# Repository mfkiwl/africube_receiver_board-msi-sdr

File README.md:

This Repository has the Africube SDR Recever Boards V1.0 and v2 <br>
Project is compleet but boards has not been build yet 3 Feb 2021
<br>

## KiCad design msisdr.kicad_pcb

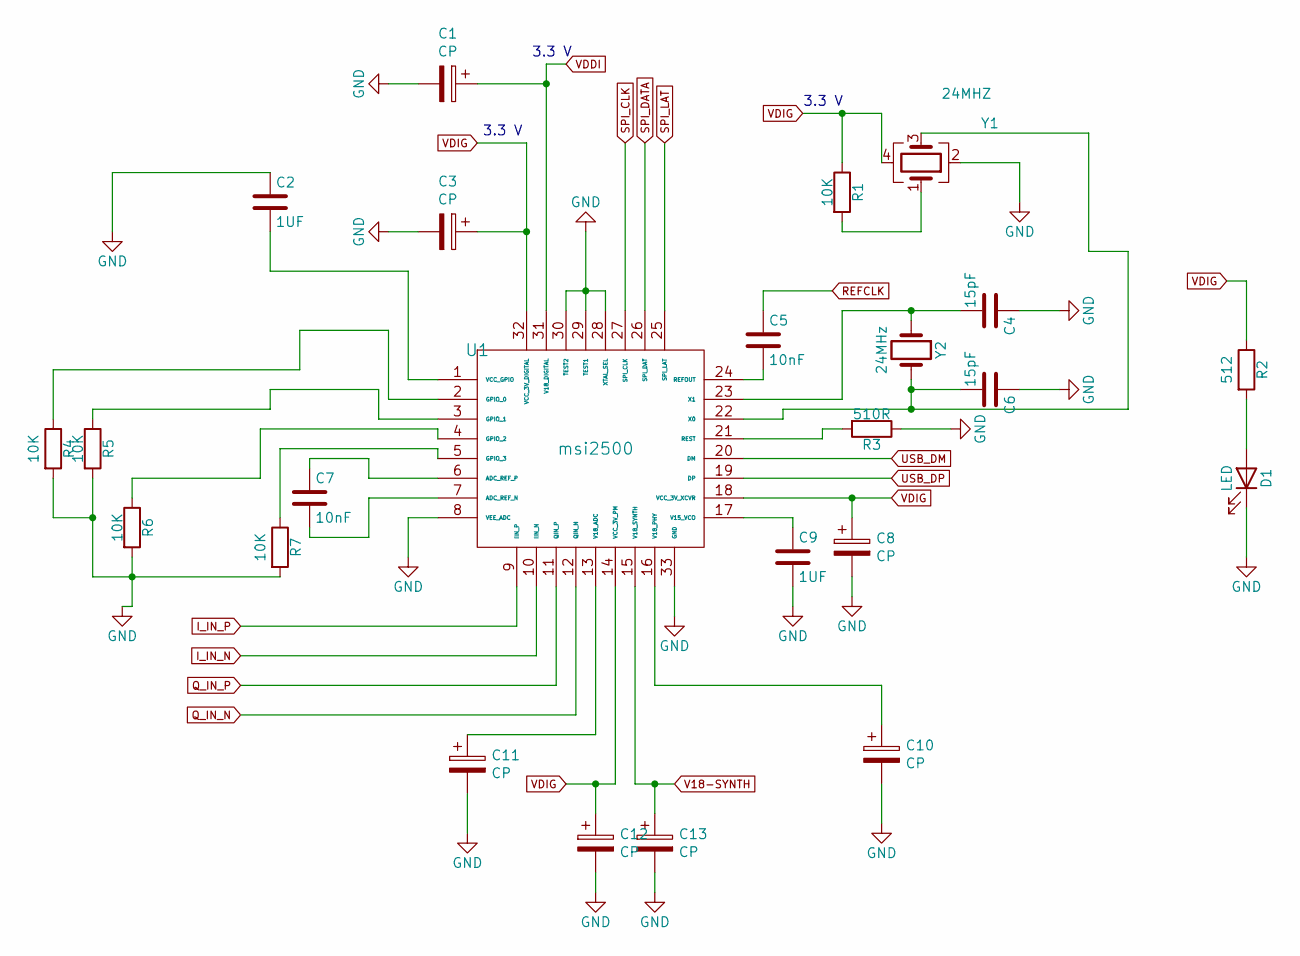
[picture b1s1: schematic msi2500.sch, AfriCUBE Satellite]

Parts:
C1, C3, C8, C10, C11, C12, C13: CP; CP_EIA-2012-12_Kemet-R
C2, C9: 1UF; C_0805_2012Metric
C4, C6: 15pF; C_0805_2012Metric
C5, C7: 10nF; C_0805_2012Metric
D1: LED; LED_0805_2012Metric
R1, R4, R5, R6, R7: 10K; R_0805_2012Metric
R2: 512; R_0805_2012Metric
R3: 510R; R_0805_2012Metric
U1: msi2500; QFN-32-1EP_5x5mm_P0.5mm_EP3.1x3.1mm
Y1: 24MHZ; Crystal_SMD_7050-4Pin_7.0x5.0mm
Y2: 24MHz; Crystal_SMD_HC49-SD

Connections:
GND: C1.2, C2.1, C3.2, C4.1, C6.1, C8.2, C9.2, C10.2, C11.2, C12.2, C13.2, D1.1 (K), R3.1, R4.2, R5.2, R6.2, R7.2, U1.8 (VEE_ADC), U1.28 (XTAL_SEL), U1.29 (TEST1), U1.30 (TEST2), U1.33 (GND), Y1.2; also elsewhere on the board
I_IN_N: U1.10 (IIN_N); also elsewhere on the board
I_IN_P: U1.9 (IIN_P); also elsewhere on the board
unnamed: C2.2, U1.1 (VCC_GPIO)
unnamed: C4.2, U1.23 (X1), Y2.1
unnamed: C5.2, U1.24 (REFOUT)
unnamed: C6.2, U1.22 (X0), Y1.3, Y2.2
unnamed: C7.1, U1.6 (ADC_REF_P)
unnamed: C7.2, U1.7 (ADC_REF_N)
unnamed: C9.1, U1.17 (V15_VCO)
unnamed: C10.1, U1.16 (V18_PHY)
unnamed: C11.1, U1.13 (V18_ADC)
unnamed: D1.2 (A), R2.2
unnamed: R1.2, Y1.1
unnamed: R3.2, U1.21 (REST)
unnamed: R4.1, U1.2 (GPIO_0)
unnamed: R5.1, U1.3 (GPIO_1)
unnamed: R6.1, U1.4 (GPIO_2)
unnamed: R7.1, U1.5 (GPIO_3)
Q_IN_N: U1.12 (QIN_N); also elsewhere on the board
Q_IN_P: U1.11 (QIN_P); also elsewhere on the board
REFCLK: C5.1; also elsewhere on the board
SPI_CLK: U1.27 (SPI_CLK); also elsewhere on the board
SPI_DATA: U1.26 (SPI_DAT); also elsewhere on the board
SPI_LAT: U1.25 (SPI_LAT); also elsewhere on the board
USB_DM: U1.20 (DM); also elsewhere on the board
USB_DP: U1.19 (DP); also elsewhere on the board
V18-SYNTH: C13.1, U1.15 (V18_SYNTH); also elsewhere on the board
VDDI: C1.1, U1.31 (V18_DIGITAL); also elsewhere on the board
VDIG: C3.1, C8.1, C12.1, R1.1, R2.1, U1.14 (VCC_3V_PM), U1.18 (VCC_3V_XCVR), U1.32 (VCC_3V_DIGITAL), Y1.4; also elsewhere on the board

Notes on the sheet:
3.3 V

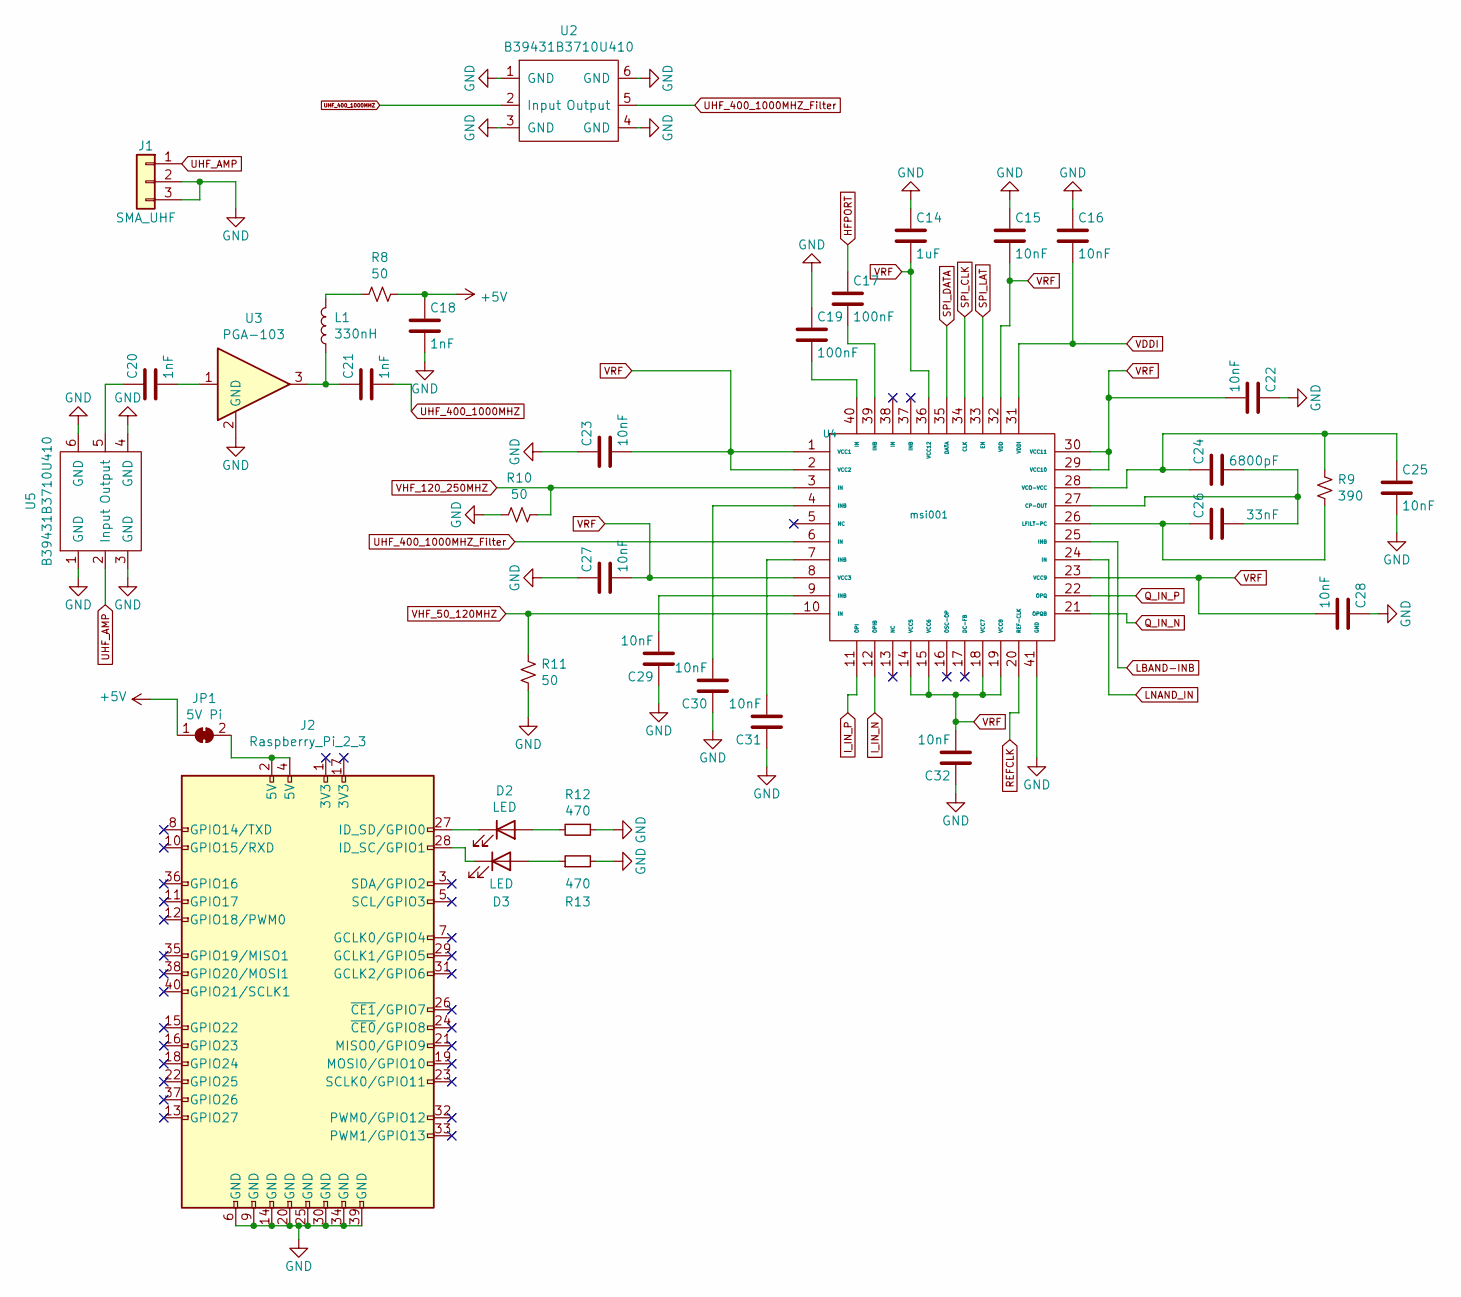
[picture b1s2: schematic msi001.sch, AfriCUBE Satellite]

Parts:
C14: 1uF; C_0805_2012Metric
C15, C16, C22, C23, C25, C27, C28, C29, C30, C31, C32: 10nF; C_0805_2012Metric
C17, C19: 100nF; C_0805_2012Metric
C18, C20, C21: 1nF; C_0805_2012Metric
C24: 6800pF; C_0805_2012Metric
C26: 33nF; C_0805_2012Metric
D2, D3: LED; LED_0805_2012Metric
J1: SMA_UHF; SMA_OPL_EMPTYHEAD
J2: Raspberry_Pi_2_3; PinHeader_2x20_P2.54mm_Vertical
JP1: 5V Pi; SolderJumper-2_P1.3mm_Bridged_RoundedPad1.0x1.5mm
L1: 330nH; L_0805_2012Metric
R8, R10, R11: 50; R_0805_2012Metric
R9: 390; R_0805_2012Metric
R12, R13: 470; R_0805_2012Metric
U2, U5: B39431B3710U410; DFN-6-1EP_3x3mm_P1mm_EP1.5x2.4mm
U3: PGA-103; SOT-89-3
U4: msi001; QFN-40-1EP_6x6mm_P0.5mm_EP4.6x4.6mm

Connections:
+5V: C18.1, JP1.1 (A), R8.1; also elsewhere on the board
GND: C14.1, C15.1, C16.1, C18.2, C19.1, C22.1, C23.1, C25.2, C27.1, C28.1, C29.1, C30.1, C31.1, C32.1, J1.2, J1.3, J2.6 (GND), J2.9 (GND), J2.14 (GND), J2.20 (GND), J2.25 (GND), J2.30 (GND), J2.34 (GND), J2.39 (GND), R10.2, R11.1, R12.1, R13.2, U2.1 (GND), U2.3 (GND), U2.4 (GND), U2.6 (GND), U3.2 (GND), U4.41 (GND), U5.1 (GND), U5.3 (GND), U5.4 (GND), U5.6 (GND); also elsewhere on the board
HFPORT: C17.1
I_IN_N: U4.12 (OPIB); also elsewhere on the board
I_IN_P: U4.11 (OPI); also elsewhere on the board
LBAND-INB: U4.25 (INB)
LNAND_IN: U4.24 (IN)
unnamed: C17.2, U4.39 (INB)
unnamed: C19.2, U4.40 (IN)
unnamed: C20.1, U5.5 (Output)
unnamed: C20.2, U3.1
unnamed: C21.1, L1.1, U3.3
unnamed: C24.1, C25.1, R9.1, U4.28 (VCO-VCC)
unnamed: C24.2, C26.2, U4.27 (CP-OUT)
unnamed: C26.1, R9.2, U4.26 (LFILT-PC)
unnamed: C29.2, U4.9 (INB)
unnamed: C30.2, U4.4 (INB)
unnamed: C31.2, U4.7 (INB)
unnamed: D2.1 (K), J2.27 (ID_SD/GPIO0)
unnamed: D2.2 (A), R12.2
unnamed: D3.1 (K), J2.28 (ID_SC/GPIO1)
unnamed: D3.2 (A), R13.1
unnamed: J2.2 (5V), J2.4 (5V), JP1.2 (B)
unnamed: L1.2, R8.2
Q_IN_N: U4.21 (OPQB); also elsewhere on the board
Q_IN_P: U4.22 (OPQ); also elsewhere on the board
REFCLK: U4.20 (REF-CLK); also elsewhere on the board
SPI_CLK: U4.34 (CLK); also elsewhere on the board
SPI_DATA: U4.35 (DATA); also elsewhere on the board
SPI_LAT: U4.33 (EN); also elsewhere on the board
UHF_400_1000MHZ: C21.2, U2.2 (Input)
UHF_400_1000MHZ_Filter: U2.5 (Output), U4.6 (IN)
UHF_AMP: J1.1, U5.2 (Input)
VDDI: C16.2, U4.31 (VDDI); also elsewhere on the board
VHF_50_120MHZ: R11.2, U4.10 (IN)
VHF_120_250MHZ: R10.1, U4.3 (IN)
VRF: C14.2, C15.2, C22.2, C23.2, C27.2, C28.2, C32.2, U4.1 (VCC1), U4.2 (VCC2), U4.8 (VCC3), U4.14 (VCC5), U4.15 (VCC6), U4.18 (VCC7), U4.19 (VCC8), U4.23 (VCC9), U4.29 (VCC10), U4.30 (VCC11), U4.32 (VDD), U4.36 (VCC12); also elsewhere on the board

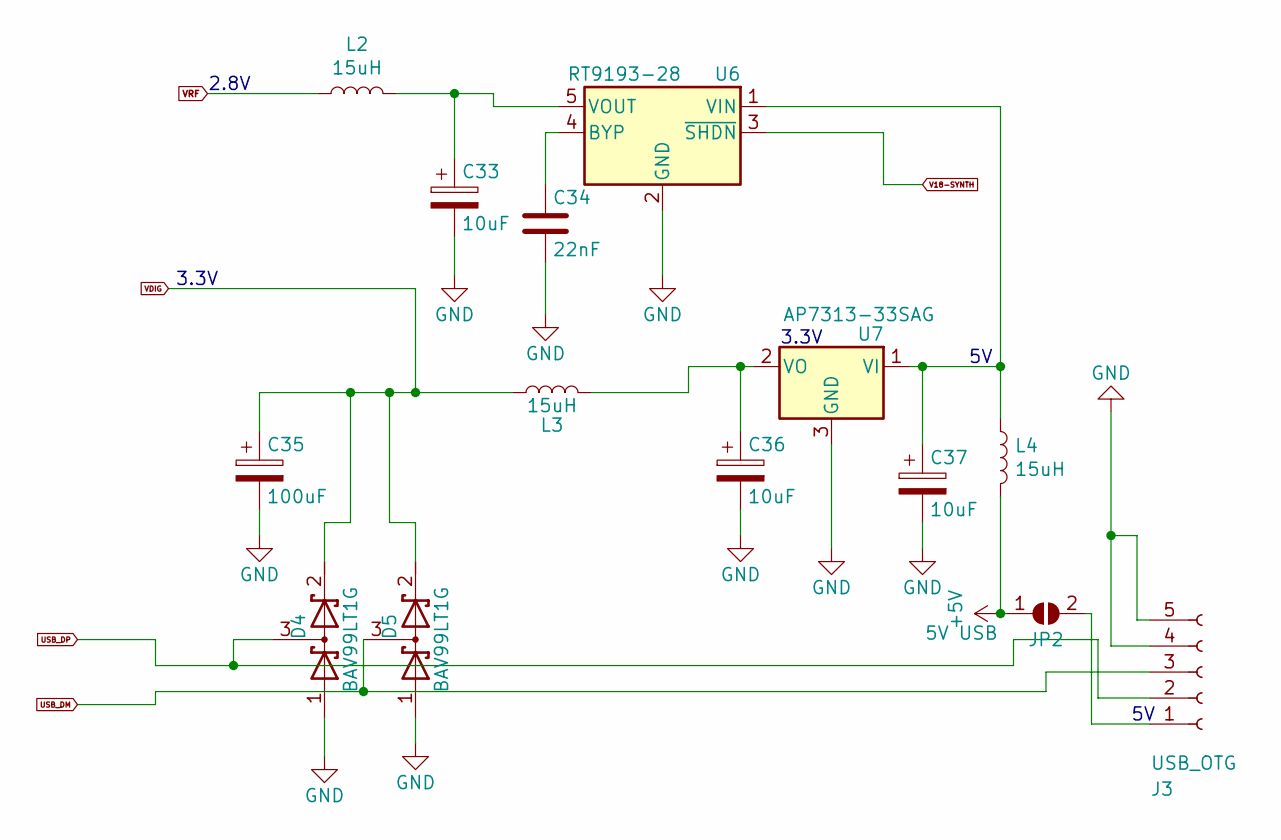
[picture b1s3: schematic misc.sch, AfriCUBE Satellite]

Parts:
C33, C36, C37: 10uF; CP_EIA-2012-12_Kemet-R
C34: 22nF; C_0805_2012Metric
C35: 100uF; CP_EIA-7343-15_Kemet-W
D4, D5: BAV99LT1G; SOT-23
J3: USB_OTG; PinHeader_1x05_P1.00mm_Vertical
JP2: 5V USB; SolderJumper-2_P1.3mm_Open_RoundedPad1.0x1.5mm
L2, L3, L4: 15uH; L_1210_3225Metric
U6: RT9193-28; SOT-23-5
U7: AP7313-33SAG; SOT-23

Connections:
+5V: JP2.1 (A), L4.2; also elsewhere on the board
GND: C33.2, C34.2, C35.2, C36.2, C37.2, D4.1 (A), D5.1 (A), J3.4, J3.5, U6.2 (GND), U7.3 (GND); also elsewhere on the board
unnamed: C33.1, L2.2, U6.5 (VOUT)
unnamed: C34.1, U6.4 (BYP)
unnamed: C36.1, L3.2, U7.2 (VO)
unnamed: C37.1, L4.1, U6.1 (VIN), U7.1 (VI)
unnamed: J3.1, JP2.2 (B)
USB_DM: D5.3 (common), J3.3; also elsewhere on the board
USB_DP: D4.3 (common), J3.2; also elsewhere on the board
V18-SYNTH: U6.3 (~SHDN~); also elsewhere on the board
VDIG: C35.1, D4.2 (K), D5.2 (K), L3.1; also elsewhere on the board
VRF: L2.1; also elsewhere on the board

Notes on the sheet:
3.3V
2.8V

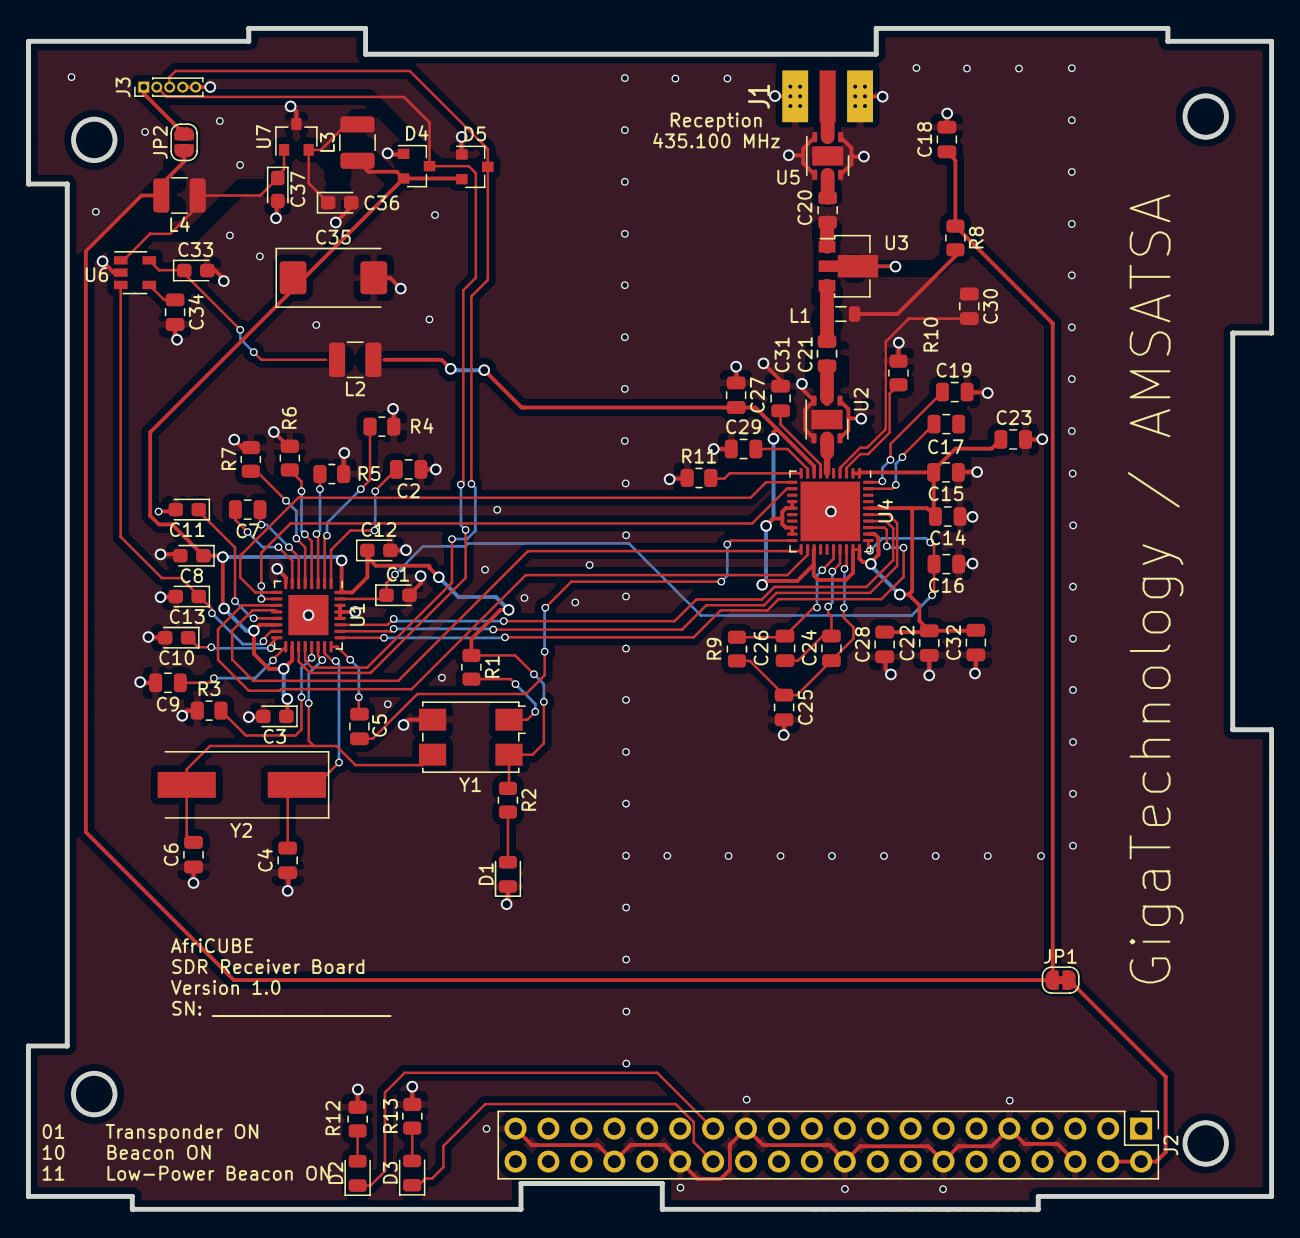
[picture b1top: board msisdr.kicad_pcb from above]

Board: 2 copper layers, 95.9 x 91.1 mm, 73 parts (0 on the bottom side), 59 nets.
